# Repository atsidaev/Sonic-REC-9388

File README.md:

# Sonic REC-9388

Sonic REC-9388 - это один из "клавиатурных" клонов Nintendo Famicom, вдохновленных Nintendo Family Basic. Построен на отдельных микросхемах CPU/PPU - UM6527 и UM6538, хотя встречается и вариант с SECAM PPU в виде впаянной на место 6538 дочерней платы, на которой расположены UM6558 и UM6559.

Эта модель Sonic получила распространение в г. Екатеринбурге и окрестностях (продавалась фирмой, расположенной в г. Верхняя Пышма). Иных каналов поставки в Россию, по-видимому, не было.

Характерной особенностью REC-9388 являются три дополнительных слота под картриджи особого (ни с чем не совместимосго) формата, на которых записаны программы, работающие с клавиатурой. Три картриджа поставлялось в комплекте с самим компьютером, о существовании каких-то либо ещё неизвестно.

В этом репозитории я собираюсь складывать имеющуюся информацию о Сонике.

## Картриджи с софтом

У меня есть парочка "ненужных" картриджей для Соника, один из них был распаян и плата отсканирована. Вот схема (неполная, только то, что вызвонилось на ногах EEPROM):

Была прочитана сама микросхема, содержимое полностью совпало с ранее полученным [здесь](https://www.emu-land.net/forum/index.php/topic,210.550.html#lastPost) (благодарности murgatroid_79, evgeny и Rumata). Мой дамп и дампы двух остальных картриджей с emu-land размещены [в этой директории](https://github.com/atsidaev/Sonic-REC-9388/tree/master/Cards/roms).

По сканам платы ([перед](https://raw.githubusercontent.com/atsidaev/Sonic-REC-9388/master/Cards/images/PCB_Front.png), [зад](https://raw.githubusercontent.com/atsidaev/Sonic-REC-9388/master/Cards/images/PCB_Back.png)) была отрисована плата (SprintLayout -> KiCAD):

Платы получены, одна собрана и подтверждена работоспособность. В корпус влазят внатяг, но и оригинальные тоже сидят крайне плотно.

## Клавиатура

Благодаря [@murgatroid79](https://github.com/murgatroid79), [пожертвовавшему свою плату](https://github.com/atsidaev/Sonic-REC-9388/issues/1) на благо реверс-инжиниринга, удалось восстановить схему клавиатуры. Kicad проект лежит [в этой директории](https://github.com/atsidaev/Sonic-REC-9388/tree/master/Keyboard/hardware). Также там есть плата, но это лишь рабочий вариант, полученный в процессе реверса, я не стремился следовать оригинальному пути дорожек и игнорировал все полигоны. Ну и, конечно, эта плата рассчитана под оригинальные кнопки, что сразу сводит на ноль её реальную полезность. Но как начальный вариант для дальнейшей переразводки под современные механические свичи вполне годится.

Схема клавиатуры достаточно оригинальна.

Вместо одной 4017, как в оригинале и большинстве клонов, тут используется пара 74161 + 74145. Вероятно, это связано с тем, что создателям был нужен ряд №11, который достаточно любопытно реализован как монтажное И двух разрядов счетчика 161.

[Схема в PDF](https://raw.githubusercontent.com/atsidaev/Sonic-REC-9388/master/Keyboard/hardware/sonic-rec9388-keyboard.pdf)

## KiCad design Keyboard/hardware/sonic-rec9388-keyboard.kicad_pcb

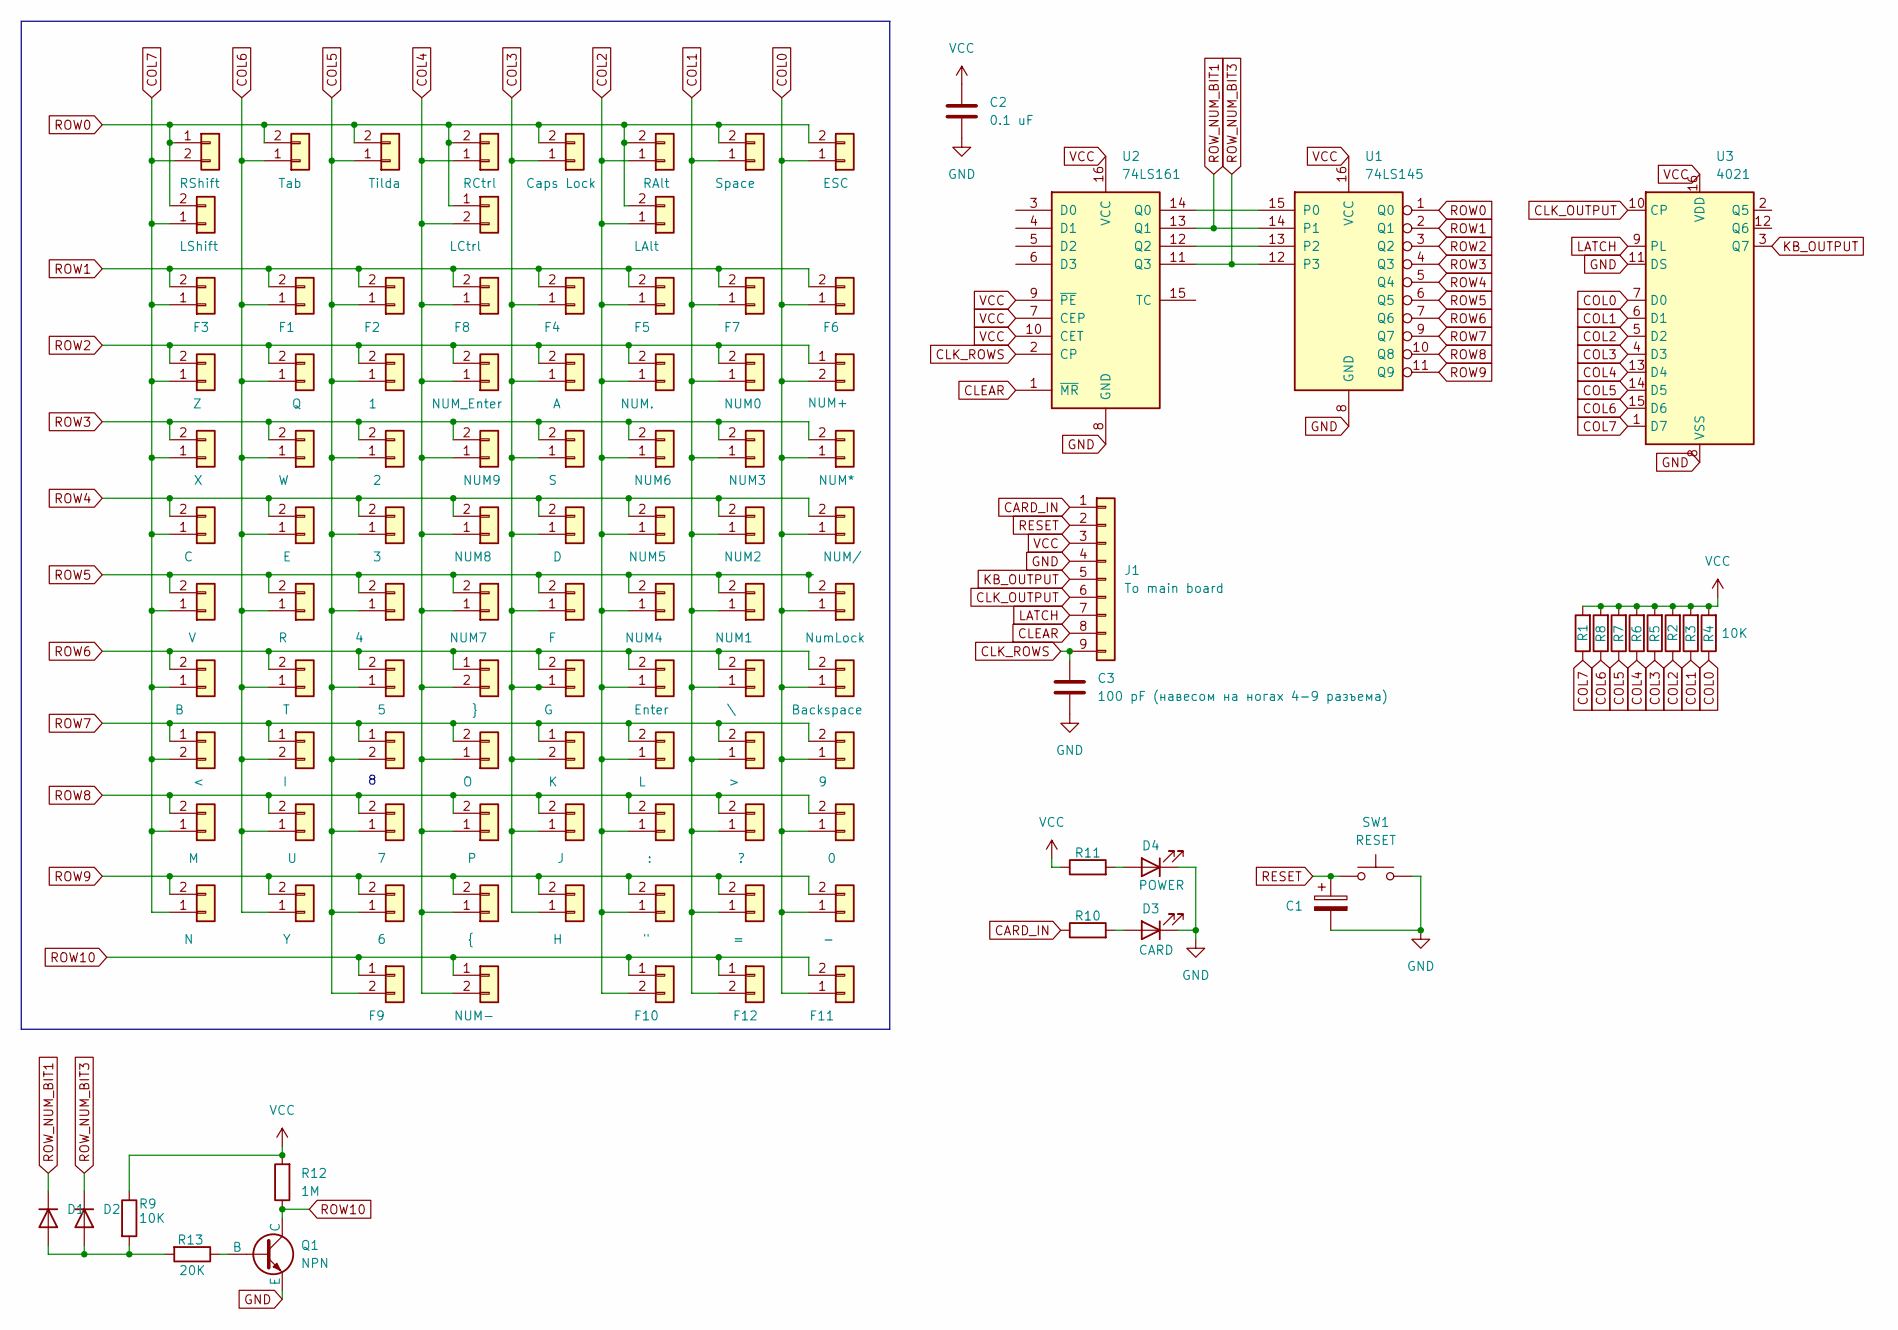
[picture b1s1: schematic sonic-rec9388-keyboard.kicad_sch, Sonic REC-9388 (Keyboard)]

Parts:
BTN1: >; KEYB_BUTTON
BTN2: LAlt; KEYB_BUTTON
BTN3: "; KEYB_BUTTON
BTN4: ?; KEYB_BUTTON
BTN5: E; KEYB_BUTTON
BTN6: G; KEYB_BUTTON
BTN7: }; KEYB_BUTTON
BTN8: =; KEYB_BUTTON
BTN9: -; KEYB_BUTTON
BTN10: 6; KEYB_BUTTON
BTN11: 1; KEYB_BUTTON
BTN12: <; KEYB_BUTTON
BTN13: J; KEYB_BUTTON
BTN14: Enter; KEYB_BUTTON
BTN15: H; KEYB_BUTTON
BTN16: W; KEYB_BUTTON
BTN17: F; KEYB_BUTTON
BTN18: R; KEYB_BUTTON
BTN19: {; KEYB_BUTTON
BTN20: 0; KEYB_BUTTON
BTN21: 5; KEYB_BUTTON
BTN22: F2; KEYB_BUTTON
BTN23: M; KEYB_BUTTON
BTN24: C; KEYB_BUTTON
BTN25: :; KEYB_BUTTON
BTN26: Z; KEYB_BUTTON
BTN27: Q; KEYB_BUTTON
BTN28: D; KEYB_BUTTON
BTN29: Y; KEYB_BUTTON
BTN30: P; KEYB_BUTTON
BTN31: 9; KEYB_BUTTON
BTN32: 4; KEYB_BUTTON
BTN33: Tilda; KEYB_BUTTON
BTN34: B; KEYB_BUTTON
BTN35: X; KEYB_BUTTON
BTN36: L; KEYB_BUTTON
BTN37: LShift; KEYB_BUTTON
BTN38: Tab; KEYB_BUTTON
BTN39: S; KEYB_BUTTON
BTN40: T; KEYB_BUTTON
BTN41: O; KEYB_BUTTON
BTN42: 8; KEYB_BUTTON
BTN43: 3; KEYB_BUTTON
BTN44: F1; KEYB_BUTTON
BTN45: N; KEYB_BUTTON
BTN46: V; KEYB_BUTTON
BTN47: K; KEYB_BUTTON
BTN48: LCtrl; KEYB_BUTTON
BTN49: Caps Lock; KEYB_BUTTON
BTN50: A; KEYB_BUTTON
BTN51: U; KEYB_BUTTON
BTN52: I; KEYB_BUTTON
BTN53: 7; KEYB_BUTTON
BTN54: 2; KEYB_BUTTON
BTN55: ESC; KEYB_BUTTON
BTN56: F4; KEYB_BUTTON
BTN57: F5; KEYB_BUTTON
BTN58: F8; KEYB_BUTTON
BTN59: F9; KEYB_BUTTON
BTN60: F10; KEYB_BUTTON
BTN61: F11; KEYB_BUTTON
BTN62: RCtrl; KEYB_BUTTON
BTN63: RShift; KEYB_BUTTON
BTN64: \; KEYB_BUTTON
BTN65: NUM1; KEYB_BUTTON
BTN66: NUM2; KEYB_BUTTON
BTN67: F3; KEYB_BUTTON
BTN68: F6; KEYB_BUTTON
BTN69: F7; KEYB_BUTTON
BTN70: F12; KEYB_BUTTON
BTN71: Space; KEYB_BUTTON
BTN72: RAlt; KEYB_BUTTON
BTN73: NUM0; KEYB_BUTTON
BTN74: NUM+; KEYB_BUTTON
BTN75: NUM_Enter; KEYB_BUTTON
BTN76: NUM.; KEYB_BUTTON
BTN77: NUM3; KEYB_BUTTON
BTN78: NUM-; KEYB_BUTTON
BTN79: NUM*; KEYB_BUTTON
BTN80: NUM/; KEYB_BUTTON
BTN81: NumLock; KEYB_BUTTON
BTN82: Backspace; KEYB_BUTTON
BTN83: NUM9; KEYB_BUTTON
BTN84: NUM8; KEYB_BUTTON
BTN85: NUM7; KEYB_BUTTON
BTN86: NUM6; KEYB_BUTTON
BTN87: NUM5; KEYB_BUTTON
BTN88: NUM4; KEYB_BUTTON
C1: C_Polarized; CP_Radial_D5.0mm_P2.50mm
C2: 0.1 uF; C_Rect_L9.0mm_W2.5mm_P7.50mm_MKT
C3: 100 pF (навесом на ногах 4-9 разъема); CAPACITOR-3.75
D1, D2: D; R_Axial_DIN0207_L6.3mm_D2.5mm_P10.16mm_Horizontal
D3: CARD; LED_D3.0mm
D4: POWER; LED_D3.0mm
J1: To main board; PinHeader_1x09_P2.54mm_Vertical
Q1: NPN; TO-92L_Inline_Wide
R1, R2, R3, R4, R5, R6, R7, R8, R9: 10K; R_Axial_DIN0207_L6.3mm_D2.5mm_P10.16mm_Horizontal
R10, R11: 100; R_Axial_DIN0207_L6.3mm_D2.5mm_P10.16mm_Horizontal
R12: 1M; R_Axial_DIN0207_L6.3mm_D2.5mm_P10.16mm_Horizontal
R13: 20K; R_Axial_DIN0207_L6.3mm_D2.5mm_P10.16mm_Horizontal
SW1: RESET; RESET_BTN
U1: 74LS145; DIP-16_W7.62mm_LongPads
U2: 74LS161; DIP-16_W7.62mm_LongPads
U3: 4021; DIP-16_W7.62mm_LongPads

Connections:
CARD_IN: J1.1, R10.1
CLEAR: J1.8, U2.1 (~MR)
CLK_OUTPUT: J1.6, U3.10 (CP)
CLK_ROWS: C3.1, J1.9, U2.2 (CP)
COL0: BTN9.1, BTN20.1, BTN31.1, BTN55.1, BTN61.1, BTN68.1, BTN74.2, BTN79.1, BTN80.1, BTN81.1, BTN82.1, R4.1, U3.7 (D0)
COL1: BTN1.1, BTN4.1, BTN8.1, BTN64.1, BTN65.1, BTN66.1, BTN69.1, BTN70.2, BTN71.1, BTN73.1, BTN77.1, R3.1, U3.6 (D1)
COL2: BTN2.1, BTN3.1, BTN14.1, BTN25.1, BTN36.1, BTN57.1, BTN60.2, BTN72.1, BTN76.1, BTN86.1, BTN87.1, BTN88.1, R2.1, U3.5 (D2)
COL3: BTN6.1, BTN13.1, BTN15.1, BTN17.1, BTN28.1, BTN39.1, BTN47.2, BTN49.1, BTN50.1, BTN56.1, R5.1, U3.4 (D3)
COL4: BTN7.2, BTN19.1, BTN30.1, BTN41.1, BTN48.2, BTN58.1, BTN62.1, BTN75.1, BTN78.2, BTN83.1, BTN84.1, BTN85.1, R6.1, U3.13 (D4)
COL5: BTN10.1, BTN11.1, BTN21.1, BTN22.1, BTN32.1, BTN33.1, BTN42.2, BTN43.1, BTN53.1, BTN54.1, BTN59.2, R7.1, U3.14 (D5)
COL6: BTN5.1, BTN16.1, BTN18.1, BTN27.1, BTN29.1, BTN38.1, BTN40.1, BTN44.1, BTN51.1, BTN52.2, R8.1, U3.15 (D6)
COL7: BTN12.2, BTN23.1, BTN24.1, BTN26.1, BTN34.1, BTN35.1, BTN37.1, BTN45.1, BTN46.1, BTN63.2, BTN67.1, R1.1, U3.1 (D7)
GND: C1.2, C2.2, C3.2, D3.1 (K), D4.1 (K), J1.4, Q1.3 (E), SW1.2, U1.8 (GND), U2.8 (GND), U3.8 (VSS), U3.11 (DS)
KB_OUTPUT: J1.5, U3.3 (Q7)
LATCH: J1.7, U3.9 (PL)
unnamed: D1.2 (A), D2.2 (A), R9.2, R13.2
unnamed: D3.2 (A), R10.2
unnamed: D4.2 (A), R11.2
unnamed: Q1.2 (B), R13.1
unnamed: U1.15 (P0), U2.14 (Q0)
unnamed: U1.13 (P2), U2.12 (Q2)
RESET: C1.1, J1.2, SW1.1
ROW0: BTN2.2, BTN33.2, BTN37.2, BTN38.2, BTN48.1, BTN49.2, BTN55.2, BTN62.2, BTN63.1, BTN71.2, BTN72.2, U1.1 (Q0)
ROW1: BTN22.2, BTN44.2, BTN56.2, BTN57.2, BTN58.2, BTN67.2, BTN68.2, BTN69.2, U1.2 (Q1)
ROW2: BTN11.2, BTN26.2, BTN27.2, BTN50.2, BTN73.2, BTN74.1, BTN75.2, BTN76.2, U1.3 (Q2)
ROW3: BTN16.2, BTN35.2, BTN39.2, BTN54.2, BTN77.2, BTN79.2, BTN83.2, BTN86.2, U1.4 (Q3)
ROW4: BTN5.2, BTN24.2, BTN28.2, BTN43.2, BTN66.2, BTN80.2, BTN84.2, BTN87.2, U1.5 (Q4)
ROW5: BTN17.2, BTN18.2, BTN32.2, BTN46.2, BTN65.2, BTN81.2, BTN85.2, BTN88.2, U1.6 (Q5)
ROW6: BTN6.2, BTN7.1, BTN14.2, BTN21.2, BTN34.2, BTN40.2, BTN64.2, BTN82.2, U1.7 (Q6)
ROW7: BTN1.2, BTN12.1, BTN31.2, BTN36.2, BTN41.2, BTN42.1, BTN47.1, BTN52.1, U1.9 (Q7)
ROW8: BTN4.2, BTN13.2, BTN20.2, BTN23.2, BTN25.2, BTN30.2, BTN51.2, BTN53.2, U1.10 (Q8)
ROW9: BTN3.2, BTN8.2, BTN9.2, BTN10.2, BTN15.2, BTN19.2, BTN29.2, BTN45.2, U1.11 (Q9)
ROW10: BTN59.1, BTN60.1, BTN61.2, BTN70.1, BTN78.1, Q1.1 (C), R12.1
ROW_NUM_BIT1: D1.1 (K), U1.14 (P1), U2.13 (Q1)
ROW_NUM_BIT3: D2.1 (K), U1.12 (P3), U2.11 (Q3)
VCC: C2.1, J1.3, R1.2, R2.2, R3.2, R4.2, R5.2, R6.2, R7.2, R8.2, R9.1, R11.1, R12.2, U1.16 (VCC), U2.7 (CEP), U2.9 (~PE), U2.10 (CET), U2.16 (VCC), U3.16 (VDD)

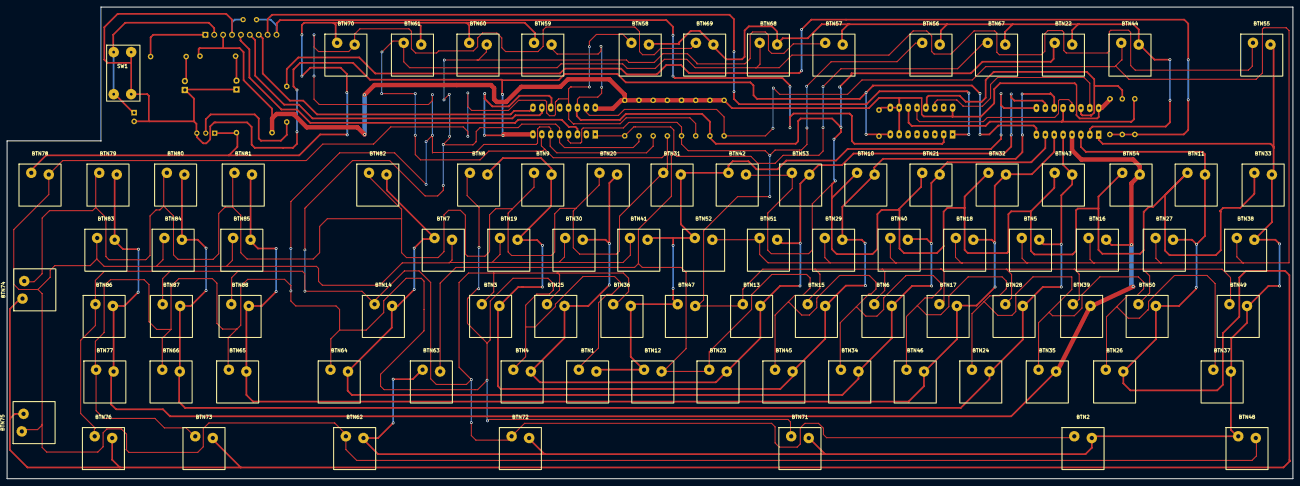
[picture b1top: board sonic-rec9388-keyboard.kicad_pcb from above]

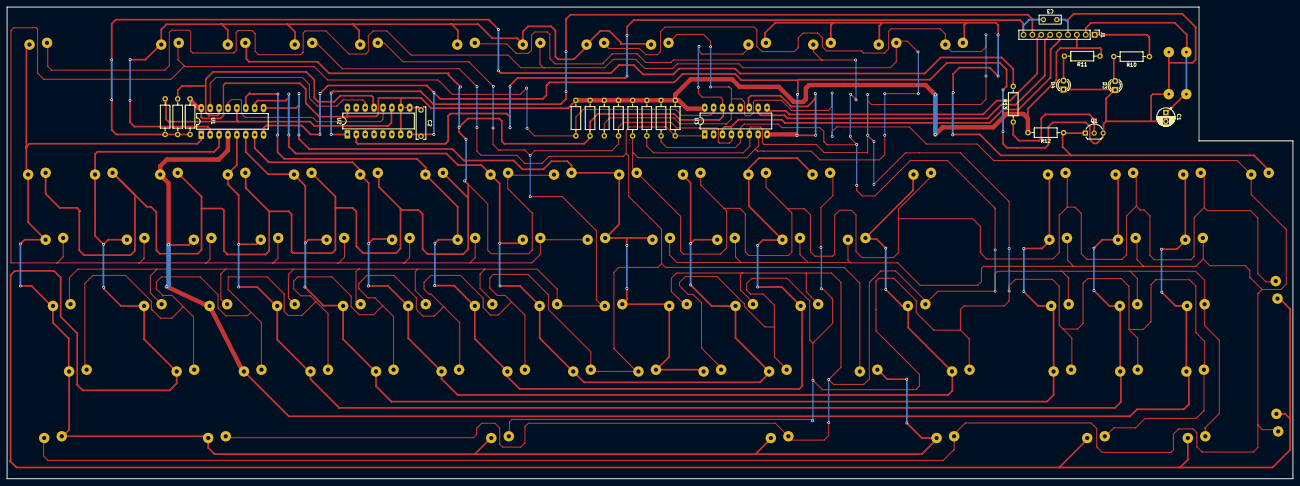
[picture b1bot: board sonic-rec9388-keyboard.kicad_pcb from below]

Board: 2 copper layers, 367.0 x 134.6 mm, 114 parts (25 on the bottom side), 36 nets.

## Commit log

2023-01-29 Add card PCB and Schematics
2023-01-29 Add ROM files for inner cards
2023-01-29 Add card PCB photos
2023-01-29 Gerber added
2023-01-29 Add README.md
2023-01-29 Add License (CC-BY-SA 4.0)
2025-09-07 Add common Kicad custom footprints
2025-09-07 Add keyboard schematics & reversed PCB
2025-09-07 Update readme, add keyboard schematics
2025-09-07 Update README.md: add urls
2025-09-07 Add cart photo
2025-09-07 Fix reset capacitor polarity
